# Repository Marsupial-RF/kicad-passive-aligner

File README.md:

# 🇦🇷 Passive Aligner for KiCad 🇦🇷

**Rotate and reposition a series resistor, capacitor, or inductor so its pad axis follows the local connection path.** The plugin straightens its existing track chains, preserves pad identities, nets, layers and widths, and checks the proposed change with KiCad DRC before applying it.

Built by [Marsupial RF](https://marsupialrf.com) in Argentina. MIT licensed. No AI service, account, network connection, OpenEMS, or external Python package is needed. KiCad's Python, wxPython and `kicad-cli` are required. Tested on **KiCad 10.0.7 / Linux**; other versions and operating systems are not yet qualified.

## Use it

1. Select a routed **R, C or L footprint**, or one of its pads, in the PCB Editor. Enable **Footprints** in the selection filter if necessary.
2. Open **Tools → External Plugins → Passive Aligner**, or click its toolbar icon.
3. Review **Existing** and **Proposed**. The plugin projects the pad midpoint onto the line between its two local connection anchors and aligns the pad axis with that line. Each splitter branch gets its own anchors.
4. Press **Check DRC**. This runs KiCad on isolated before/after copies, with the saved project settings and custom rules. New DRC findings block **Apply alignment**.
5. Press **Apply alignment**. Review the board, then save it yourself. The plugin does not save over your board. It also stores a snapshot under `.passive-aligner-backups/` beside the board, including existing project/rule files. KiCad's ActionPlugin runner manages the normal undo transaction; the on-disk backup is independent of undo.

The preview is a connection diagram, not a copper or field rendering. The generic example below is exported from the actual before/after KiCad boards. It illustrates geometry, not measured RF performance.

## Install

Download the release ZIP and extract the **`passive_aligner`** directory into a user scripting-plugin directory shown by KiCad's **Preferences → PCB Editor → Action Plugins → Open Plugin Directory**. Alternatively, copy that directory from this repository. Refresh plugins or reopen the PCB Editor after saving your work. Do not install a second nested `passive_aligner/passive_aligner` directory.

Ensure that a **matching version** of `kicad-cli` is on the environment PATH used to launch KiCad. For bundled or nonstandard installations, set `PASSIVE_ALIGNER_KICAD_CLI` to its executable path before launching KiCad. No installation-specific paths are embedded in the plugin.

## Agent / command-line use

The same geometry and DRC code is available without controlling the GUI. Use a Python interpreter able to `import pcbnew` from your KiCad installation:

```bash
# Inspect the plan; input stays untouched.
python align.py board.kicad_pcb --reference R1

# Apply only after DRC passes, to a NEW output file.
python align.py board.kicad_pcb --reference R1 --output aligned.kicad_pcb

# Optional explicit executable; references can be repeated for independent paths.
python align.py board.kicad_pcb --reference R1 --reference C2 \
  --kicad-cli /path/to/kicad-cli --output aligned.kicad_pcb
```

Output is JSON. Exit 0 means the requested operation succeeded, 1 means invalid input or an execution failure, and 2 means DRC rejected a proposed change. A plan-only command can succeed with no changes; inspect `changes` and `skipped`. Existing output boards and sidecars are never overwritten. An agent or MCP executor can invoke this CLI; it is not itself an MCP server.

## Scope

- Exactly two numbered SMD pads, on one outer copper layer, with distinct assigned nets. Bottom-side components are supported.
- Existing, unlocked straight-track chains must terminate at pad centres. Each chain keeps a constant width and layer. The next external pad, via, or explicit endpoint junction is its anchor. Pad/net associations are never swapped to choose a shorter angle.
- Ambiguous connections, interior branches, arcs, width transitions, ground-connected shunts, pads touching filled zones, and locked items are skipped. Multiple selected components sharing a connection must be handled separately. Unrouted footprints have no reliable anchors and are skipped.
- No obstacle shoving: a new short, clearance error, courtyard collision, or other new DRC signature blocks the correction. Existing findings remain visible and are not certified away. Save project/rule changes before checking. KiCad's configured ignored checks remain ignored; the plugin does not replace your rules.
- Straightening changes electrical length. It does **not** preserve matched delay, tune impedance, certify RF performance, or replace electromagnetic simulation. Do not apply it to tuned filters or matched-length networks without reviewing those constraints.

## Reproduce the checks

```bash
python tests/test_alignment.py
python tests/test_plugin_flow.py
python tests/make_demo.py
```

The 11 geometry/DRC tests cover rotated layouts, reversed pad numbers, bottom copper, locked/shunt/ambiguous cases, unchanged net identity, explicit branch anchors, and a real DRC rejection of a new obstacle collision. The separate GUI test exercises the modal Check DRC → Apply workflow and backup without overwriting the original. `make_demo.py` generates the public synthetic boards and captures the actual plugin dialog; the GUI scripts need a display (Xvfb works for CI). The board exports use KiCad CLI; no company board is included.

KiCad's save/connectivity helpers can propagate net assignments across touching copper. Validation uses the direct board serializer and additionally compares pad/track net identities after the CLI check, so a reassigned net cannot conceal a newly introduced short. Python embedders that import the package outside KiCad must set `PASSIVE_ALIGNER_HEADLESS=1`; the provided CLI and tests do this themselves.

Contributions and issue reports are welcome. Include the KiCad version and a minimal board you are allowed to share. This is an initial geometry tool, not a general autorouter.

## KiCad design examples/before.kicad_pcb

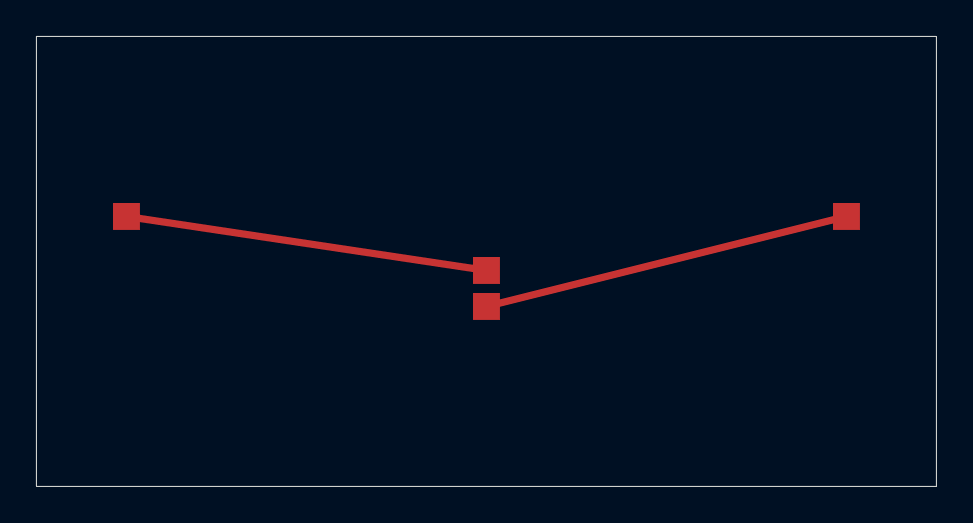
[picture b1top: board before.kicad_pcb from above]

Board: 2 copper layers, 50.0 x 25.0 mm, 3 parts (0 on the bottom side), 2 nets.

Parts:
J1, J2: TEST
R1: 49.9

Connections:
INPUT: J1.1, R1.1
OUTPUT: J2.1, R1.2
